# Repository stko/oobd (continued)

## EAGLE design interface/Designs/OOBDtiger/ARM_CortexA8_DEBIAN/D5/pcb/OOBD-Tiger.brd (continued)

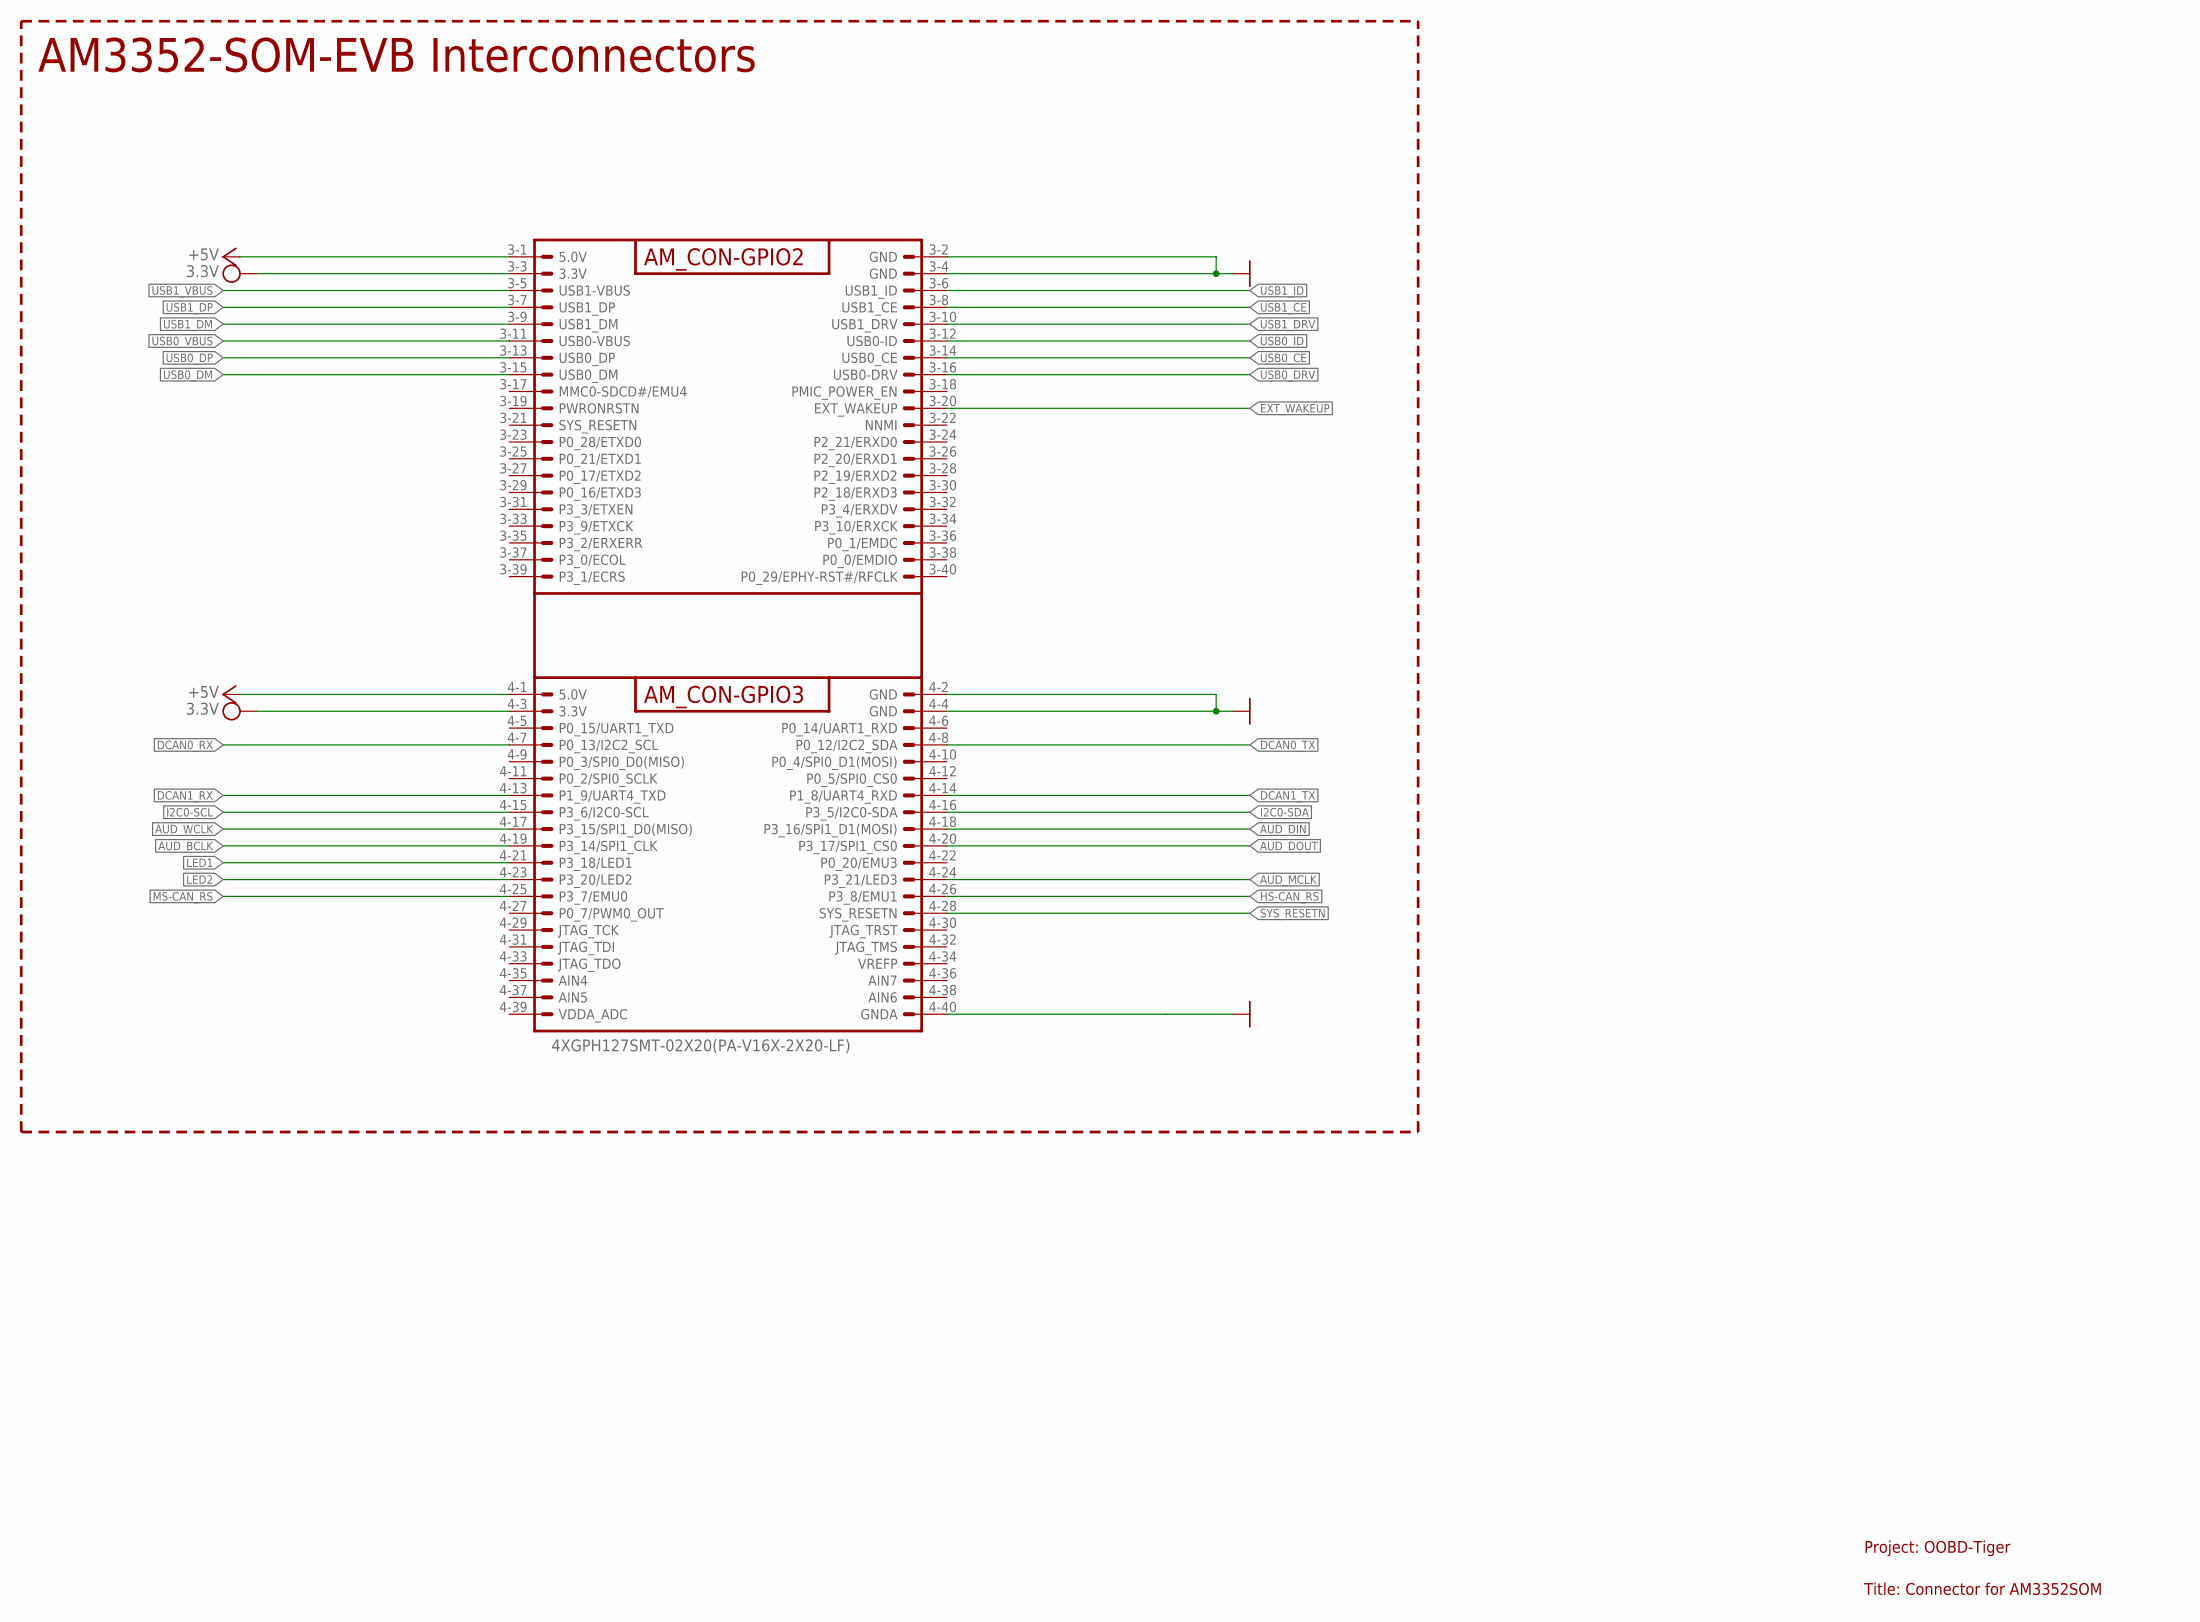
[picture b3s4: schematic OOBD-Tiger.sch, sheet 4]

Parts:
AM3352-SOM-EVB-PLATFORM: 4XGPH127SMT-02X20(PA-V16X-2X20-LF); OOBD-TIGER-AM3352-SOM

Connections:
+5V: AM3352-SOM-EVB-PLATFORM.3-1 (5.0V), AM3352-SOM-EVB-PLATFORM.4-1 (5.0V); also elsewhere on the board
AUD_BCLK: AM3352-SOM-EVB-PLATFORM.4-19 (P3_14/SPI1_CLK); also elsewhere on the board
AUD_DIN: AM3352-SOM-EVB-PLATFORM.4-18 (P3_16/SPI1_D1(MOSI)); also elsewhere on the board
AUD_DOUT: AM3352-SOM-EVB-PLATFORM.4-20 (P3_17/SPI1_CS0); also elsewhere on the board
AUD_MCLK: AM3352-SOM-EVB-PLATFORM.4-24 (P3_21/LED3); also elsewhere on the board
AUD_WCLK: AM3352-SOM-EVB-PLATFORM.4-17 (P3_15/SPI1_D0(MISO)); also elsewhere on the board
DCAN0_RX: AM3352-SOM-EVB-PLATFORM.4-7 (P0_13/I2C2_SCL); also elsewhere on the board
DCAN0_TX: AM3352-SOM-EVB-PLATFORM.4-8 (P0_12/I2C2_SDA); also elsewhere on the board
DCAN1_RX: AM3352-SOM-EVB-PLATFORM.4-13 (P1_9/UART4_TXD); also elsewhere on the board
DCAN1_TX: AM3352-SOM-EVB-PLATFORM.4-14 (P1_8/UART4_RXD); also elsewhere on the board
EXT_WAKEUP: AM3352-SOM-EVB-PLATFORM.3-20 (EXT_WAKEUP); also elsewhere on the board
GND: AM3352-SOM-EVB-PLATFORM.3-2 (GND), AM3352-SOM-EVB-PLATFORM.3-4 (GND), AM3352-SOM-EVB-PLATFORM.4-2 (GND), AM3352-SOM-EVB-PLATFORM.4-4 (GND), AM3352-SOM-EVB-PLATFORM.4-40 (GNDA); also elsewhere on the board
HS-CAN_RS: AM3352-SOM-EVB-PLATFORM.4-26 (P3_8/EMU1); also elsewhere on the board
I2C0-SCL: AM3352-SOM-EVB-PLATFORM.4-15 (P3_6/I2C0-SCL); also elsewhere on the board
I2C0-SDA: AM3352-SOM-EVB-PLATFORM.4-16 (P3_5/I2C0-SDA); also elsewhere on the board
LED1: AM3352-SOM-EVB-PLATFORM.4-21 (P3_18/LED1); also elsewhere on the board
LED2: AM3352-SOM-EVB-PLATFORM.4-23 (P3_20/LED2); also elsewhere on the board
MS-CAN_RS: AM3352-SOM-EVB-PLATFORM.4-25 (P3_7/EMU0); also elsewhere on the board
SYS_RESETN: AM3352-SOM-EVB-PLATFORM.4-28 (SYS_RESETN); also elsewhere on the board
USB0_CE: AM3352-SOM-EVB-PLATFORM.3-14 (USB0_CE); also elsewhere on the board
USB0_DM: AM3352-SOM-EVB-PLATFORM.3-15 (USB0_DM); also elsewhere on the board
USB0_DP: AM3352-SOM-EVB-PLATFORM.3-13 (USB0_DP); also elsewhere on the board
USB0_DRV: AM3352-SOM-EVB-PLATFORM.3-16 (USB0-DRV); also elsewhere on the board
USB0_ID: AM3352-SOM-EVB-PLATFORM.3-12 (USB0-ID); also elsewhere on the board
USB0_VBUS: AM3352-SOM-EVB-PLATFORM.3-11 (USB0-VBUS); also elsewhere on the board
USB1_CE: AM3352-SOM-EVB-PLATFORM.3-8 (USB1_CE); also elsewhere on the board
USB1_DM: AM3352-SOM-EVB-PLATFORM.3-9 (USB1_DM); also elsewhere on the board
USB1_DP: AM3352-SOM-EVB-PLATFORM.3-7 (USB1_DP); also elsewhere on the board
USB1_DRV: AM3352-SOM-EVB-PLATFORM.3-10 (USB1_DRV); also elsewhere on the board
USB1_ID: AM3352-SOM-EVB-PLATFORM.3-6 (USB1_ID); also elsewhere on the board
USB1_VBUS: AM3352-SOM-EVB-PLATFORM.3-5 (USB1-VBUS); also elsewhere on the board

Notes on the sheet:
AM3352-SOM-EVB Interconnectors
Project: OOBD-Tiger
Title: Connector for AM3352SOM

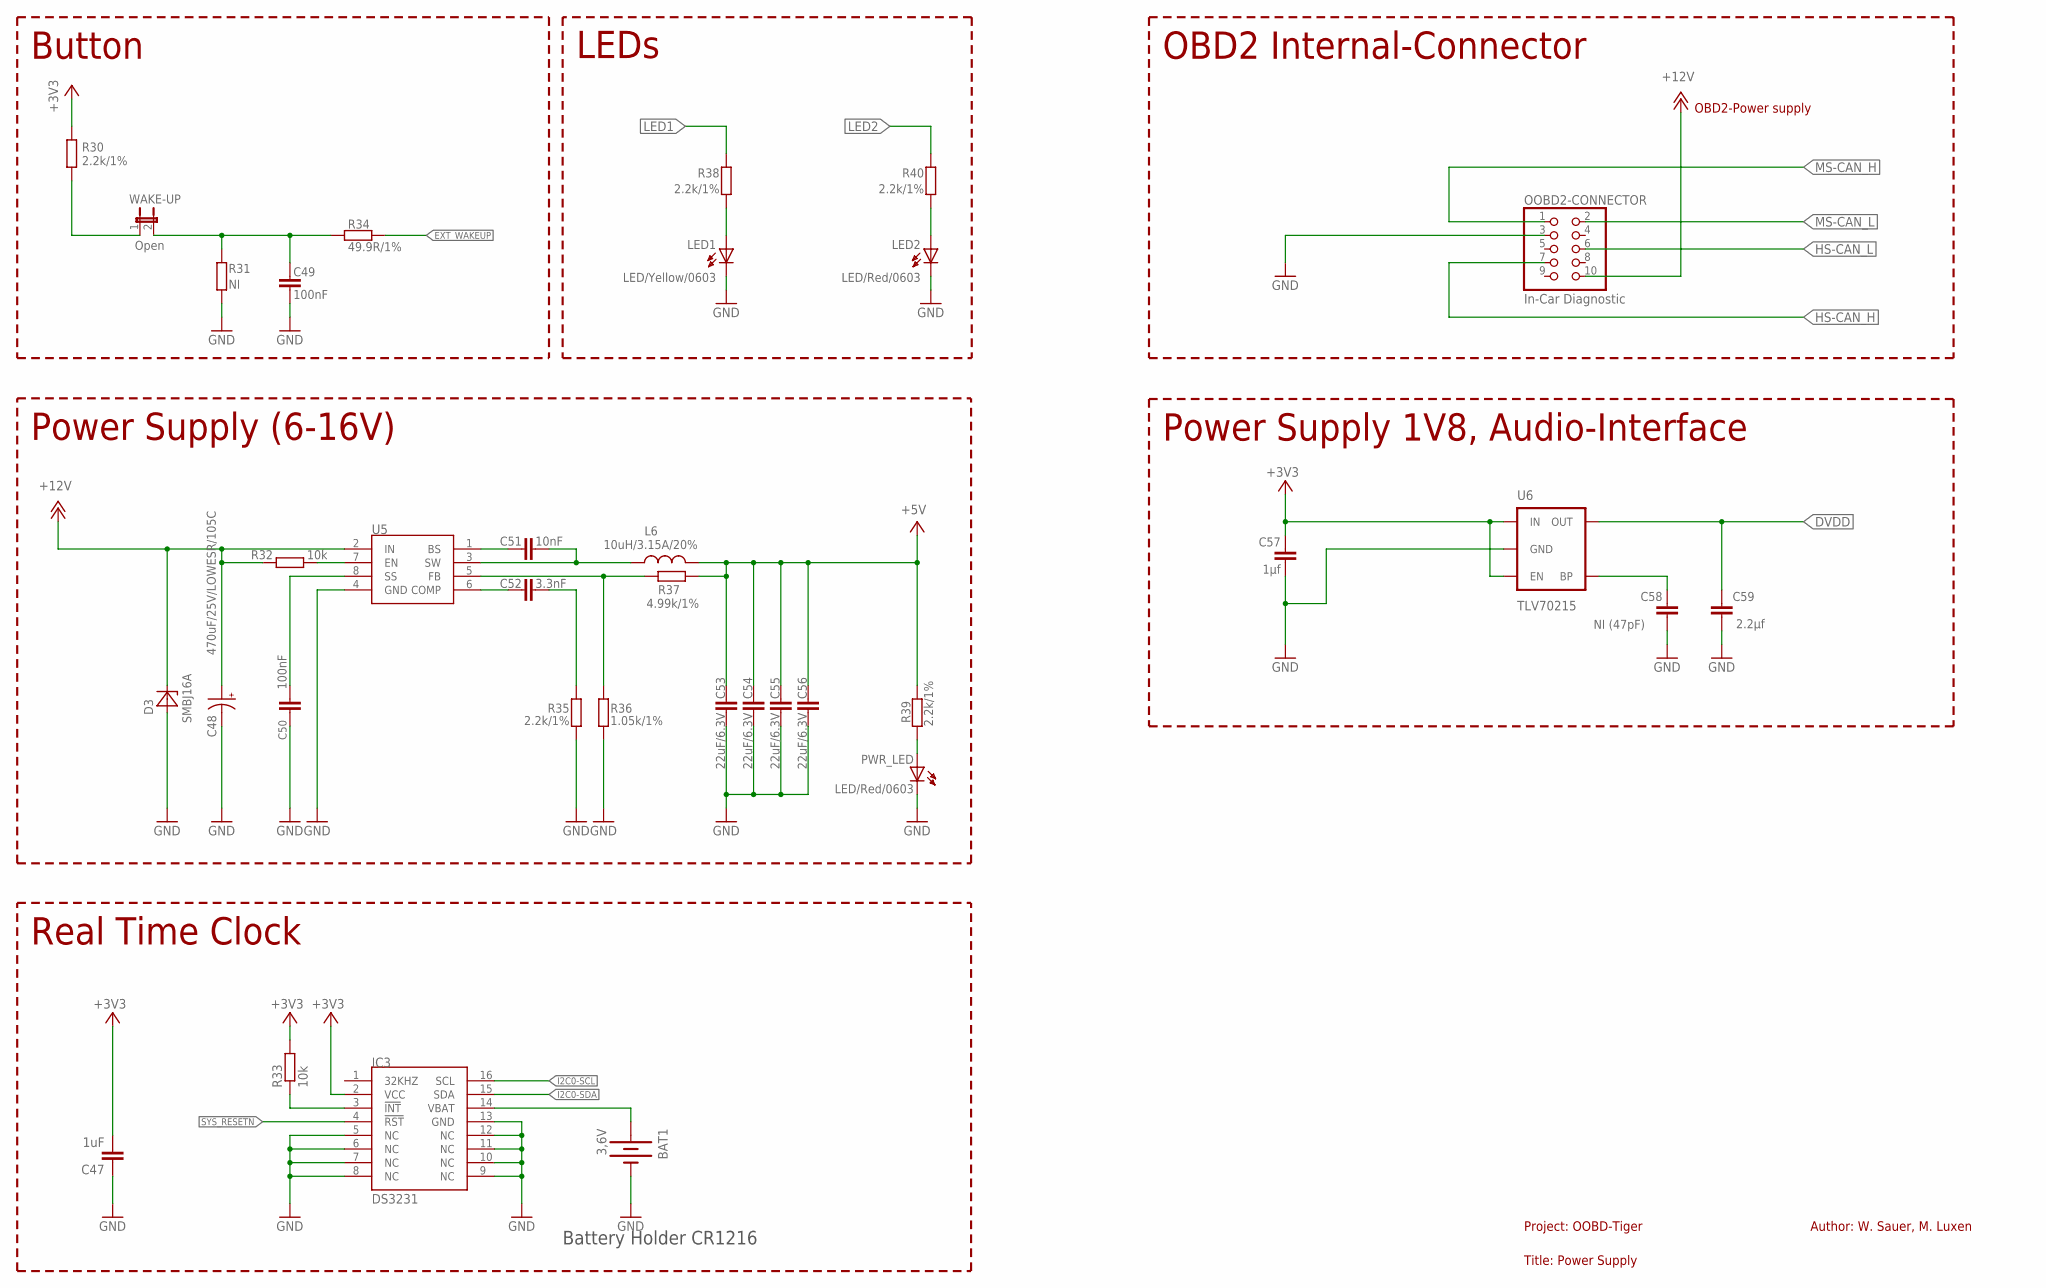
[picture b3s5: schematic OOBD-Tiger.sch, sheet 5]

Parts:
BAT1: 3,6V; BATTCON_12MM_PTH
C47: 1uF; C0603
C48: 470uF/25V/LOWESR/105C; PANASONIC_D
C49, C50: 100nF; C0603
C51: 10nF; C0603
C52: 3.3nF; C0603
C53, C54, C55, C56: 22uF/6.3V; C0603
C57: 1µf; 0603-CAP
C58: NI (47pF); 0603-CAP
C59: 2.2µf; 0603-CAP
D3: SMBJ16A; DO214AA
IC3: DS3231; SOIC-16W
L6: 10uH/3.15A/20%; 8X8MM_3131
LED1: LED/Yellow/0603; LED_0603
LED2: LED/Red/0603; LED_0603
OOBD2-CONNECTOR: In-Car Diagnostic; 2X05/90
PWR_LED: LED/Red/0603; LED-0603
R30, R35, R38, R39, R40: 2.2k/1%; R0603
R31: NI; R0603
R32, R33: 10k; R0603
R34: 49.9R/1%; R0603
R36: 1.05k/1%; R0603
R37: 4.99k/1%; R0603
U5: MP1482; SOIC8
U6: TLV70215; SOT23-5
WAKE-UP: Open; 1X02_LOCK

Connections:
+5V: C53.1, C54.1, C55.1, C56.1, L6.2, R37.2, R39.1; also elsewhere on the board
+12V: C48.+, D3.C, OOBD2-CONNECTOR.10, R32.1, U5.2 (IN)
DVDD: C59.2, U6.5 (OUT); also elsewhere on the board
EXT_WAKEUP: R34.1; also elsewhere on the board
GND: BAT1.GND (-), C47.1, C48.-, C49.2, C50.2, C53.2, C54.2, C55.2, C56.2, C57.1, C58.1, C59.1, D3.A, IC3.5 (NC), IC3.6 (NC), IC3.7 (NC), IC3.8 (NC), IC3.9 (NC), IC3.10 (NC), IC3.11 (NC), IC3.12 (NC), IC3.13 (GND), LED1.C, LED2.C, OOBD2-CONNECTOR.3, PWR_LED.C, R31.2, R35.2, R36.2, U5.4 (GND), U6.2 (GND); also elsewhere on the board
HS-CAN_H: OOBD2-CONNECTOR.7; also elsewhere on the board
HS-CAN_L: OOBD2-CONNECTOR.6; also elsewhere on the board
I2C0-SCL: IC3.16 (SCL); also elsewhere on the board
I2C0-SDA: IC3.15 (SDA); also elsewhere on the board
LED1: R38.1; also elsewhere on the board
LED2: R40.1; also elsewhere on the board
MS-CAN_H: OOBD2-CONNECTOR.1; also elsewhere on the board
MS-CAN_L: OOBD2-CONNECTOR.2; also elsewhere on the board
unnamed: LED2.A, R40.2
unnamed: C50.1, U5.8 (SS)
unnamed: R32.2, U5.7 (EN)
unnamed: C51.1, U5.1 (BS)
unnamed: C51.2, L6.1, U5.3 (SW)
unnamed: C52.1, U5.6 (COMP)
unnamed: C52.2, R35.1
unnamed: C58.2, U6.4 (BP)
unnamed: IC3.3 (!INT), R33.1
unnamed: R30.1, WAKE-UP.1
unnamed: C49.1, R31.1, R34.2, WAKE-UP.2
unnamed: R36.1, R37.1, U5.5 (FB)
unnamed: PWR_LED.A, R39.2
unnamed: LED1.A, R38.2
SYS_RESETN: IC3.4 (!RST); also elsewhere on the board
VBAT: BAT1.VCC@1 (+), IC3.14 (VBAT)

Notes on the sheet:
Button
LEDs
Power Supply (6-16V)
Author: W. Sauer, M. Luxen
Project: OOBD-Tiger
Title: Power Supply
Real Time Clock
Battery Holder CR1216
OBD2-Power supply
OBD2 Internal-Connector
Power Supply 1V8, Audio-Interface

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
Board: 2 copper layers, 101 parts (33 on the bottom side), 76 nets, no tracks yet.

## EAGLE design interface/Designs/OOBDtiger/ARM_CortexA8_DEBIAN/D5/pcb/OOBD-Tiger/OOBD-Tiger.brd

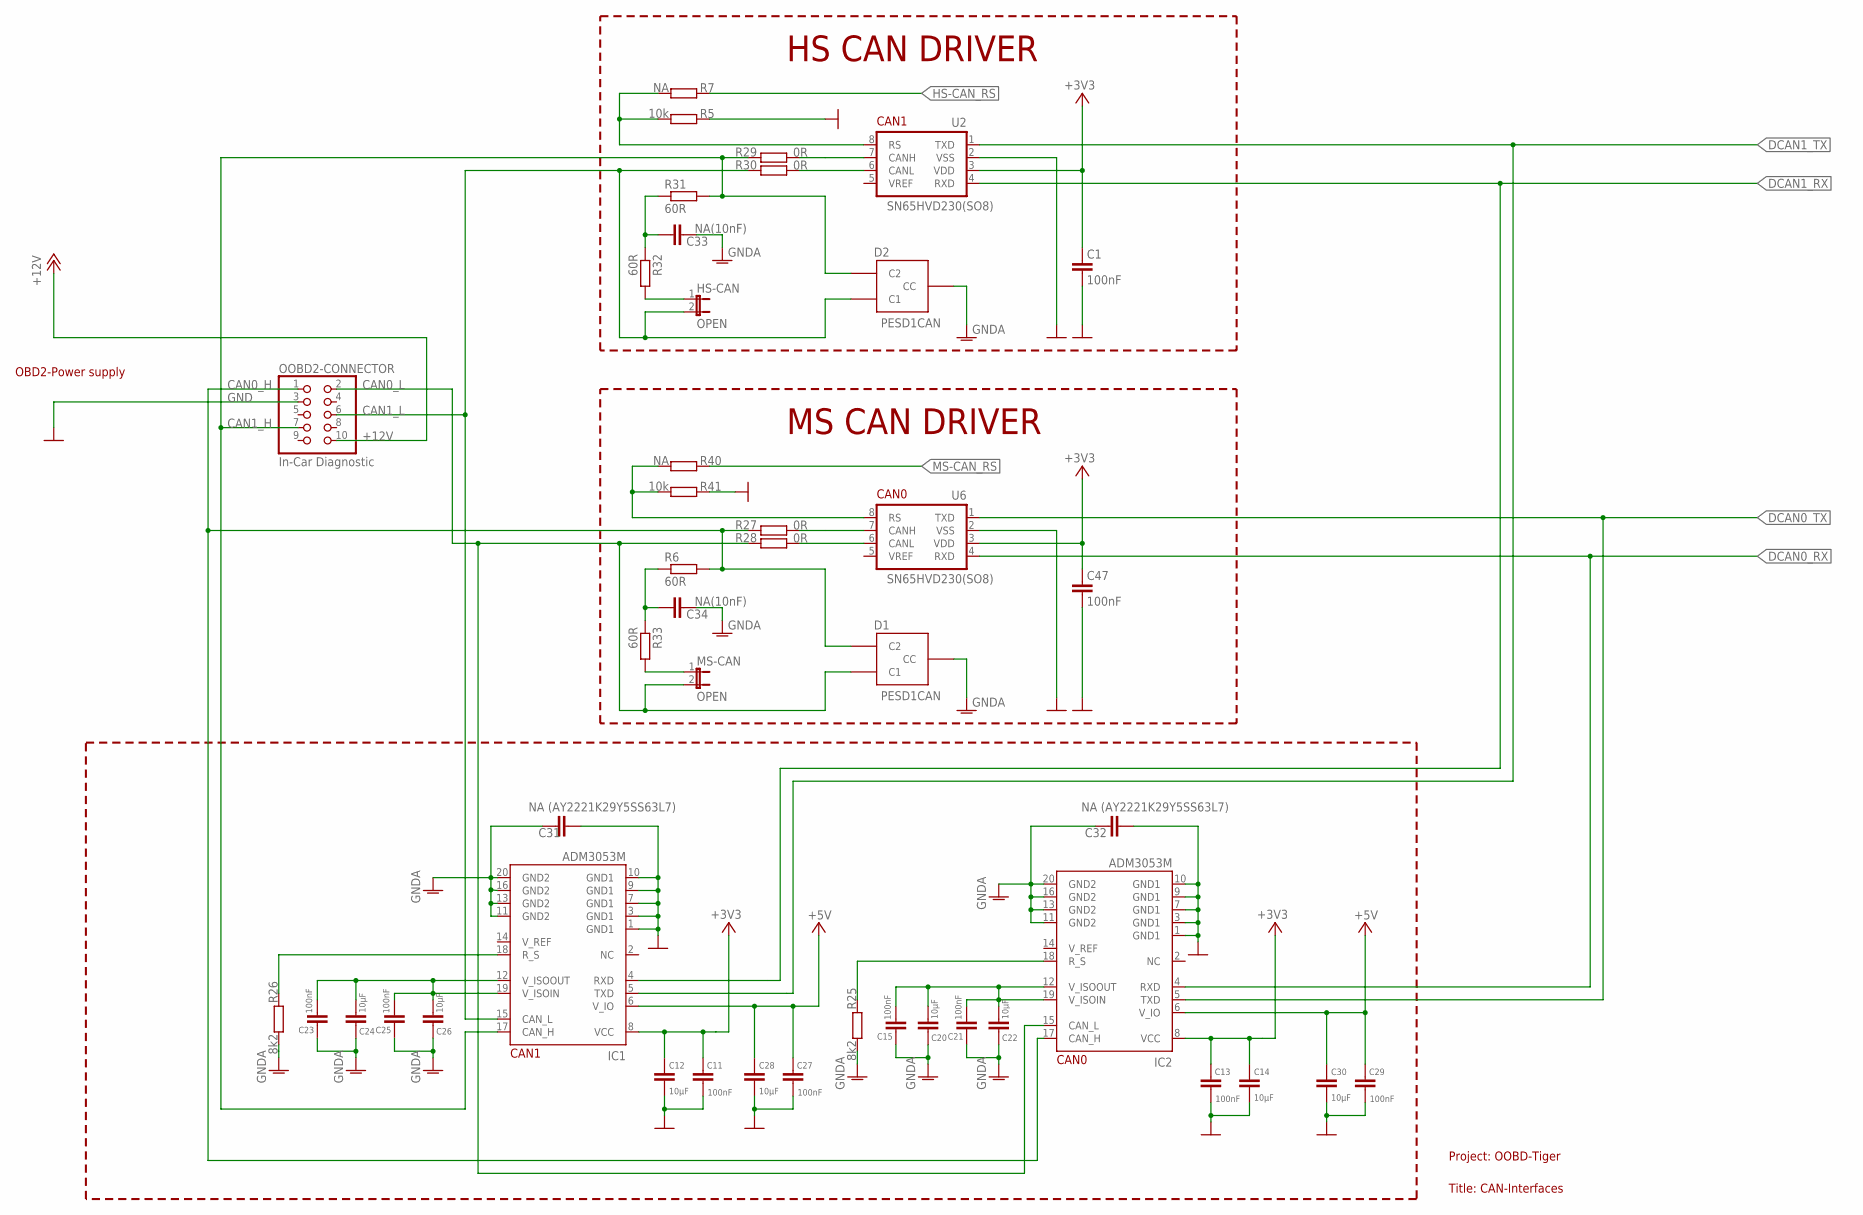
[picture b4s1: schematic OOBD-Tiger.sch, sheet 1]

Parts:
C1, C11, C13, C15, C21, C23, C25, C27, C29, C47: 100nF; C0603K
C12, C14, C20, C22, C24, C26, C28, C30: 10µF; C0805K
C31, C32: NA (AY2221K29Y5SS63L7); C075-032X103
C33, C34: NA(10nF); C0603
D1, D2: PESD1CAN; SOT23
HS-CAN: OPEN; 1X02
IC1, IC2: ADM3053M; SO20W
MS-CAN: OPEN; 1X02
OOBD2-CONNECTOR: In-Car Diagnostic; 2X05/90
R5, R41: 10k; R0603
R6, R31, R32, R33: 60R; R0603
R7, R40: NA; R0603
R25, R26: 8k2; R0603
R27, R28, R29, R30: 0R; 0207/10
U2, U6: SN65HVD230(SO8); SO-08

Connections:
+3V3: C1.1, C11.1, C12.1, C13.1, C14.1, C47.1, IC1.8 (VCC), IC2.8 (VCC), U2.3 (VDD), U6.3 (VDD); also elsewhere on the board
+5V: C27.1, C28.1, C29.1, C30.1, IC1.6 (V_IO), IC2.6 (V_IO); also elsewhere on the board
+12V: OOBD2-CONNECTOR.10; also elsewhere on the board
CAN0_H: D1.2 (C2), IC2.17 (CAN_H), OOBD2-CONNECTOR.1, R6.2, R27.1
CAN0_L: D1.1 (C1), IC2.15 (CAN_L), MS-CAN.2, OOBD2-CONNECTOR.2, R28.1
CAN1_H: D2.2 (C2), IC1.17 (CAN_H), OOBD2-CONNECTOR.7, R29.2, R31.2
CAN1_L: D2.1 (C1), HS-CAN.2, IC1.15 (CAN_L), OOBD2-CONNECTOR.6, R30.1
DCAN0_RX: IC2.4 (RXD), U6.4 (RXD); also elsewhere on the board
DCAN0_TX: IC2.5 (TXD), U6.1 (TXD); also elsewhere on the board
DCAN1_RX: IC1.4 (RXD), U2.4 (RXD); also elsewhere on the board
DCAN1_TX: IC1.5 (TXD), U2.1 (TXD); also elsewhere on the board
GND: C1.2, C11.2, C12.2, C13.2, C14.2, C27.2, C28.2, C29.2, C30.2, C31.2, C32.2, C47.2, IC1.1 (GND1), IC1.3 (GND1), IC1.7 (GND1), IC1.9 (GND1), IC1.10 (GND1), IC2.1 (GND1), IC2.3 (GND1), IC2.7 (GND1), IC2.9 (GND1), IC2.10 (GND1), OOBD2-CONNECTOR.3, R5.2, R41.2, U2.2 (VSS), U6.2 (VSS); also elsewhere on the board
GNDA: C15.2, C20.2, C21.2, C22.2, C23.2, C24.2, C25.2, C26.2, C31.1, C32.1, C33.2, C34.2, D1.3 (CC), D2.3 (CC), IC1.11 (GND2), IC1.13 (GND2), IC1.16 (GND2), IC1.20 (GND2), IC2.11 (GND2), IC2.13 (GND2), IC2.16 (GND2), IC2.20 (GND2), R25.1, R26.1
HS-CAN_RS: R7.2; also elsewhere on the board
MS-CAN_RS: R40.2; also elsewhere on the board
unnamed: C33.1, R31.1, R32.1
unnamed: R5.1, R7.1, U2.8 (RS)
unnamed: C34.1, R6.1, R33.1
unnamed: HS-CAN.1, R32.2
unnamed: C23.1, C24.1, C25.1, C26.1, IC1.12 (V_ISOOUT), IC1.19 (V_ISOIN)
unnamed: MS-CAN.1, R33.2
unnamed: IC2.18 (R_S), R25.2
unnamed: R27.2, U6.7 (CANH)
unnamed: R30.2, U2.6 (CANL)
unnamed: R28.2, U6.6 (CANL)
unnamed: R29.1, U2.7 (CANH)
unnamed: C15.1, C20.1, C21.1, C22.1, IC2.12 (V_ISOOUT), IC2.19 (V_ISOIN)
unnamed: IC1.18 (R_S), R26.2
unnamed: R40.1, R41.1, U6.8 (RS)

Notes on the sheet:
MS CAN DRIVER
HS CAN DRIVER
Project: OOBD-Tiger
Title: CAN-Interfaces
OBD2-Power supply
CAN1
CAN0

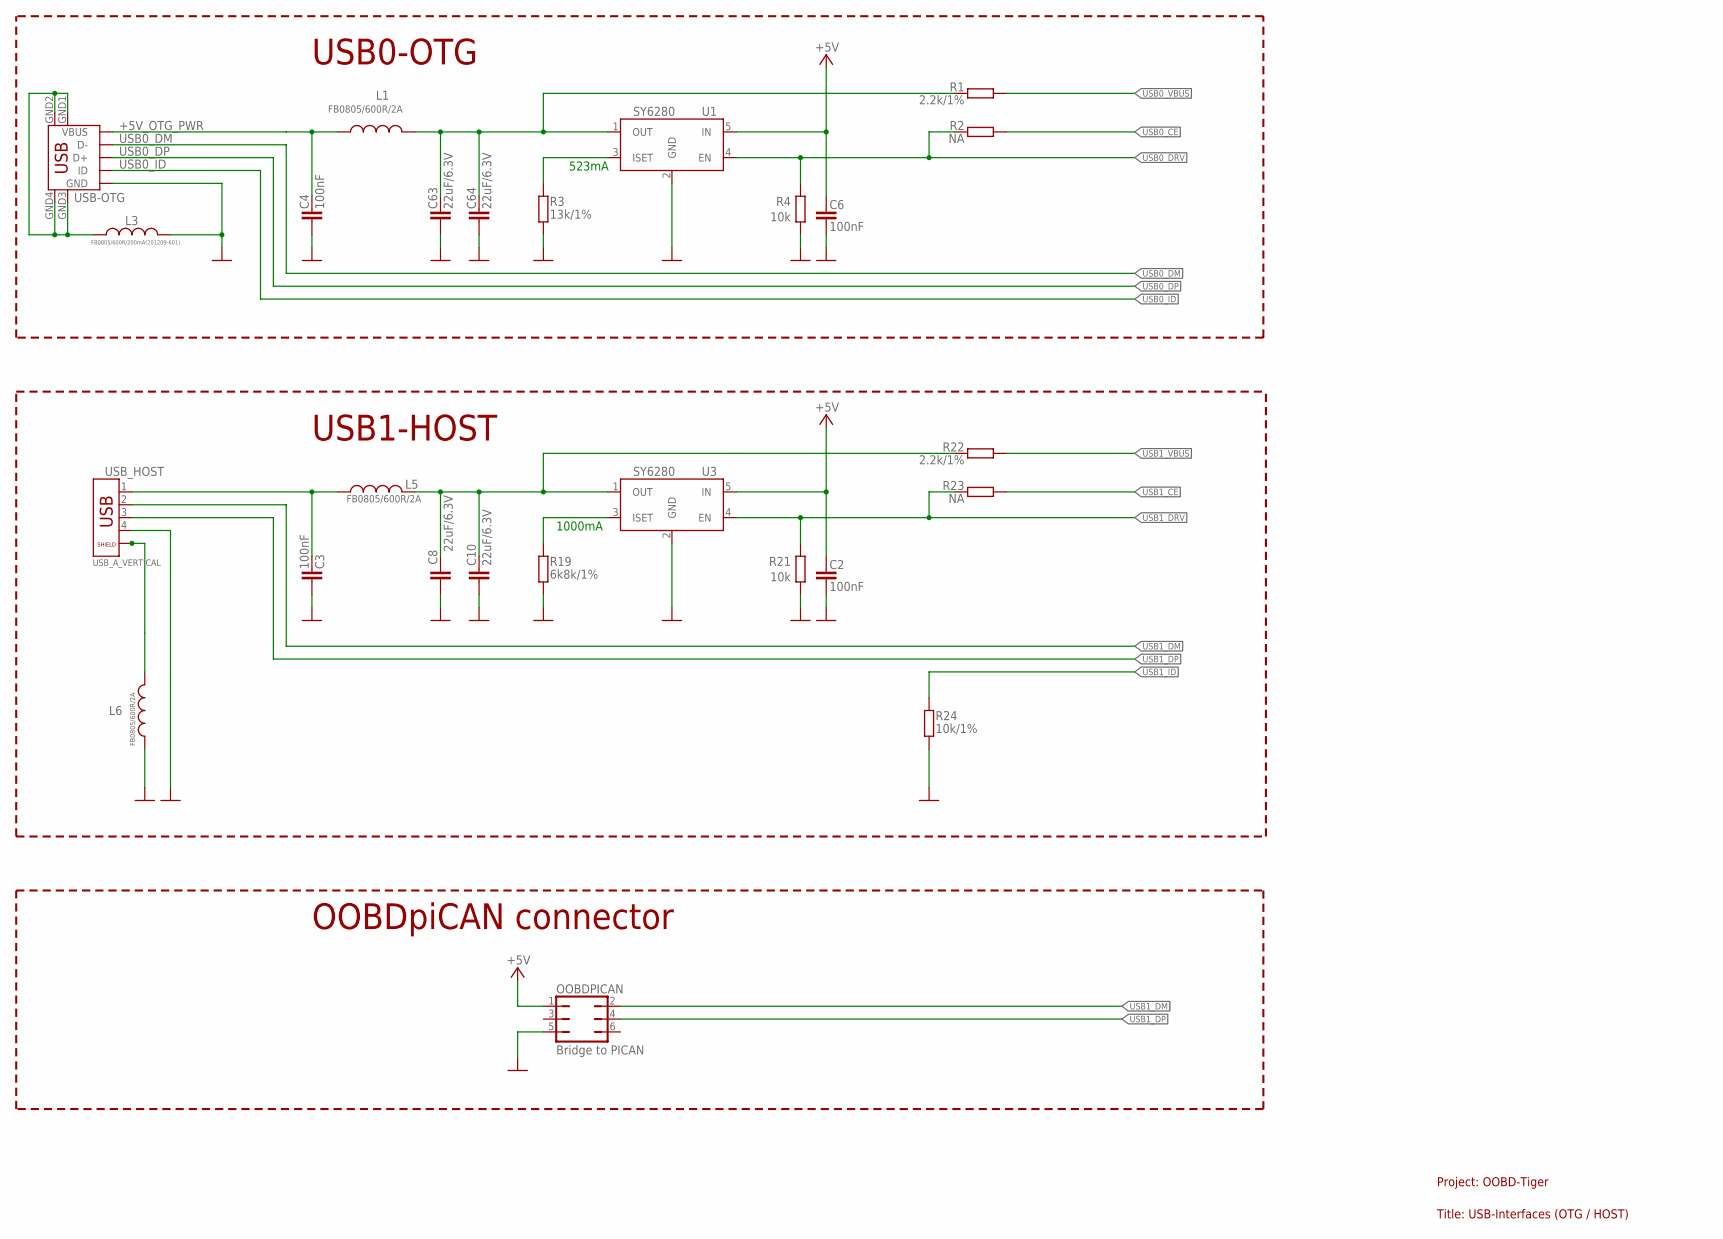
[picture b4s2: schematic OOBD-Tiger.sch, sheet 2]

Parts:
C2, C3, C4, C6: 100nF; C0603K
C8, C10, C63, C64: 22uF/6.3V; C0603
L1, L5, L6: FB0805/600R/2A; L0603
L3: FB0805/600R/200mA(201209-601); L0603
OOBDPICAN: Bridge to PICAN; JP3Q
R1, R22: 2.2k/1%; R0603
R2, R23: NA; R0603
R3: 13k/1%; R0603
R4, R21: 10k; R0603
R19: 6k8k/1%; R0603
R24: 10k/1%; R0603
U1, U3: SY6280; SOT23-5
USB_HOST: USB_A_VERTICAL; USB_PN87520_DEV_PTH
USB_OTG: USB-OTG; USB_MINI_9PIN

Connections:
+5V: C2.1, C6.1, OOBDPICAN.1, U1.5 (IN), U3.5 (IN); also elsewhere on the board
+5V_OTG_PWR: C4.1, L1.1, USB_OTG.VBUS
GND: C2.2, C3.2, C4.2, C6.2, C8.2, C10.2, C63.2, C64.2, L3.1, L6.1, OOBDPICAN.5, R3.1, R4.1, R19.1, R21.1, R24.1, U1.2 (GND), U3.2 (GND), USB_HOST.4, USB_OTG.GND; also elsewhere on the board
unnamed: R19.2, U3.3 (ISET)
unnamed: C8.1, C10.1, L5.1, R22.2, U3.1 (OUT)
unnamed: C3.1, L5.2, USB_HOST.1
unnamed: L6.2, USB_HOST.P$1 (5), USB_HOST.P$2 (6)
unnamed: R3.2, U1.3 (ISET)
unnamed: C63.1, C64.1, L1.2, R1.2, U1.1 (OUT)
unnamed: L3.2, USB_OTG.GND1, USB_OTG.GND2, USB_OTG.GND3, USB_OTG.GND4
USB0_CE: R2.2; also elsewhere on the board
USB0_DM: USB_OTG.D-; also elsewhere on the board
USB0_DP: USB_OTG.D+; also elsewhere on the board
USB0_DRV: R2.1, R4.2, U1.4 (EN); also elsewhere on the board
USB0_ID: USB_OTG.ID; also elsewhere on the board
USB0_VBUS: R1.1; also elsewhere on the board
USB1_CE: R23.2; also elsewhere on the board
USB1_DM: OOBDPICAN.2, USB_HOST.2; also elsewhere on the board
USB1_DP: OOBDPICAN.4, USB_HOST.3; also elsewhere on the board
USB1_DRV: R21.2, R23.1, U3.4 (EN); also elsewhere on the board
USB1_ID: R24.2; also elsewhere on the board
USB1_VBUS: R22.1; also elsewhere on the board

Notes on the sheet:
USB0-OTG
Project: OOBD-Tiger
Title: USB-Interfaces (OTG / HOST)
USB1-HOST
523mA
1000mA
OOBDpiCAN connector

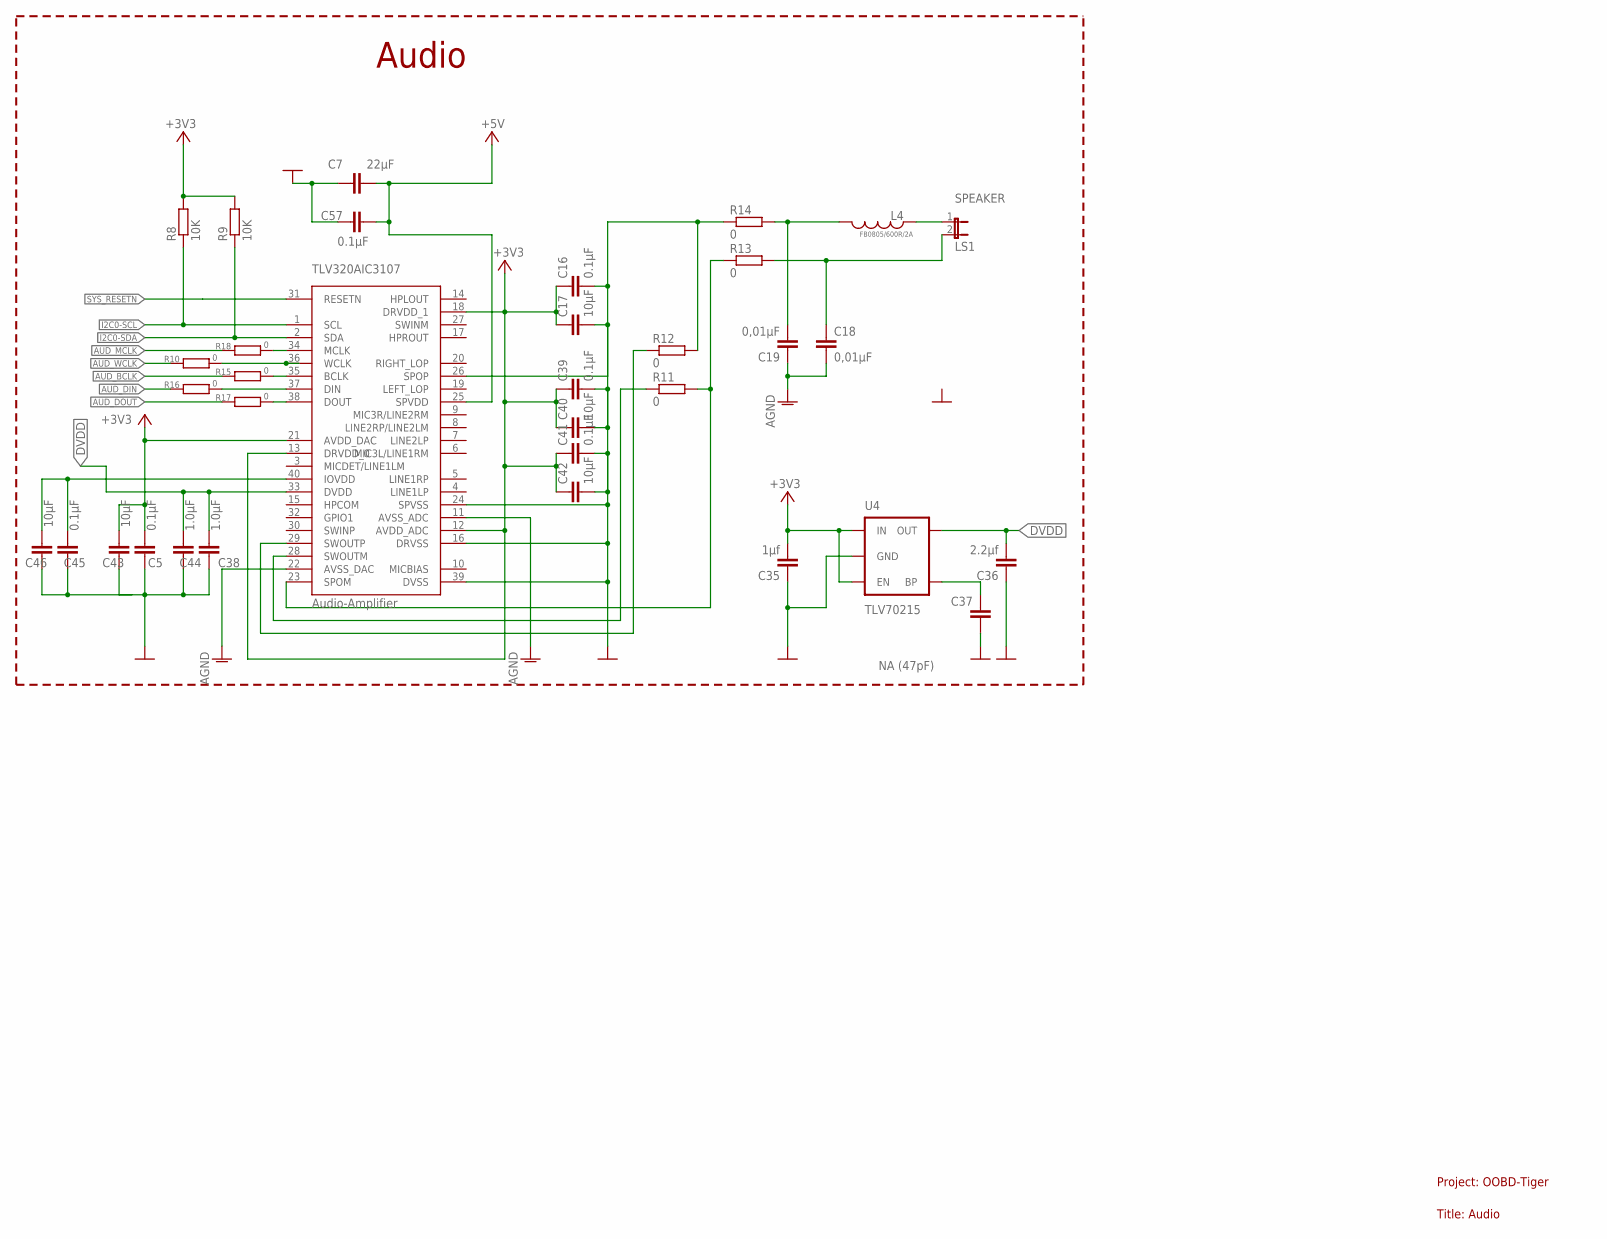
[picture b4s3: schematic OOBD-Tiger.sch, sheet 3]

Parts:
C5, C16, C39, C41, C45, C57: 0.1µF; 0603-CAP
C7: 22µF; 0603-CAP
C17, C40, C42, C43, C46: 10µF; 0603-CAP
C18, C19: 0,01µF; 0603-CAP
C35: 1µf; 0603-CAP
C36: 2.2µf; 0603-CAP
C37: NA (47pF); 0603-CAP
C38, C44: 1.0µF; 0603-CAP
L4: FB0805/600R/2A; L0603
R8, R9: 10K; R0603
R10, R11, R12, R13, R14, R15, R16, R17, R18: 0; R0603
SPEAKER: LS1; 1X02
TLV320AIC3107: Audio-Amplifier; QFN40-6X6
U4: TLV70215; SOT23-5

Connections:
+3V3: C5.2, C16.1, C17.1, C35.2, C39.1, C40.1, C41.1, C42.1, C43.2, R8.2, R9.2, TLV320AIC3107.12 (AVDD_ADC), TLV320AIC3107.13 (DRVDD_0), TLV320AIC3107.18 (DRVDD_1), TLV320AIC3107.21 (AVDD_DAC), U4.1 (IN), U4.3 (EN); also elsewhere on the board
+5V: C7.2, C57.2, TLV320AIC3107.25 (SPVDD); also elsewhere on the board
AGND: C18.2, C19.1, TLV320AIC3107.11 (AVSS_ADC), TLV320AIC3107.22 (AVSS_DAC)
AUD_BCLK: R15.1; also elsewhere on the board
AUD_DIN: R16.1; also elsewhere on the board
AUD_DOUT: R17.1; also elsewhere on the board
AUD_MCLK: R18.1; also elsewhere on the board
AUD_WCLK: R10.1; also elsewhere on the board
DVDD: C36.2, C38.2, C44.2, TLV320AIC3107.33 (DVDD), U4.5 (OUT)
GND: C5.1, C7.1, C16.2, C17.2, C35.1, C36.1, C37.1, C38.1, C39.2, C40.2, C41.2, C42.2, C43.1, C44.1, C57.1, R12.2, R14.1, TLV320AIC3107.16 (DRVSS), TLV320AIC3107.24 (SPVSS), TLV320AIC3107.26 (SPOP), TLV320AIC3107.39 (DVSS), U4.2 (GND); also elsewhere on the board
GND1: C45.1, C46.1
I2C0-SCL: R8.1, TLV320AIC3107.1 (SCL); also elsewhere on the board
I2C0-SDA: R9.1, TLV320AIC3107.2 (SDA); also elsewhere on the board
unnamed: C37.2, U4.4 (BP)
unnamed: C19.2, L4.2, R14.2
unnamed: C18.1, R13.2, SPEAKER.2
unnamed: L4.1, SPEAKER.1
unnamed: R11.2, R13.1, TLV320AIC3107.23 (SPOM)
unnamed: R11.1, TLV320AIC3107.28 (SWOUTM)
unnamed: R12.1, TLV320AIC3107.29 (SWOUTP)
unnamed: C45.2, C46.2, TLV320AIC3107.40 (IOVDD)
unnamed: R17.2, TLV320AIC3107.38 (DOUT)
unnamed: R16.2, TLV320AIC3107.37 (DIN)
unnamed: R15.2, TLV320AIC3107.35 (BCLK)
unnamed: R10.2, TLV320AIC3107.36 (WCLK)
unnamed: R18.2, TLV320AIC3107.34 (MCLK)
SYS_RESETN: TLV320AIC3107.31 (RESETN); also elsewhere on the board

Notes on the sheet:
Project: OOBD-Tiger
Title: Audio
Audio
